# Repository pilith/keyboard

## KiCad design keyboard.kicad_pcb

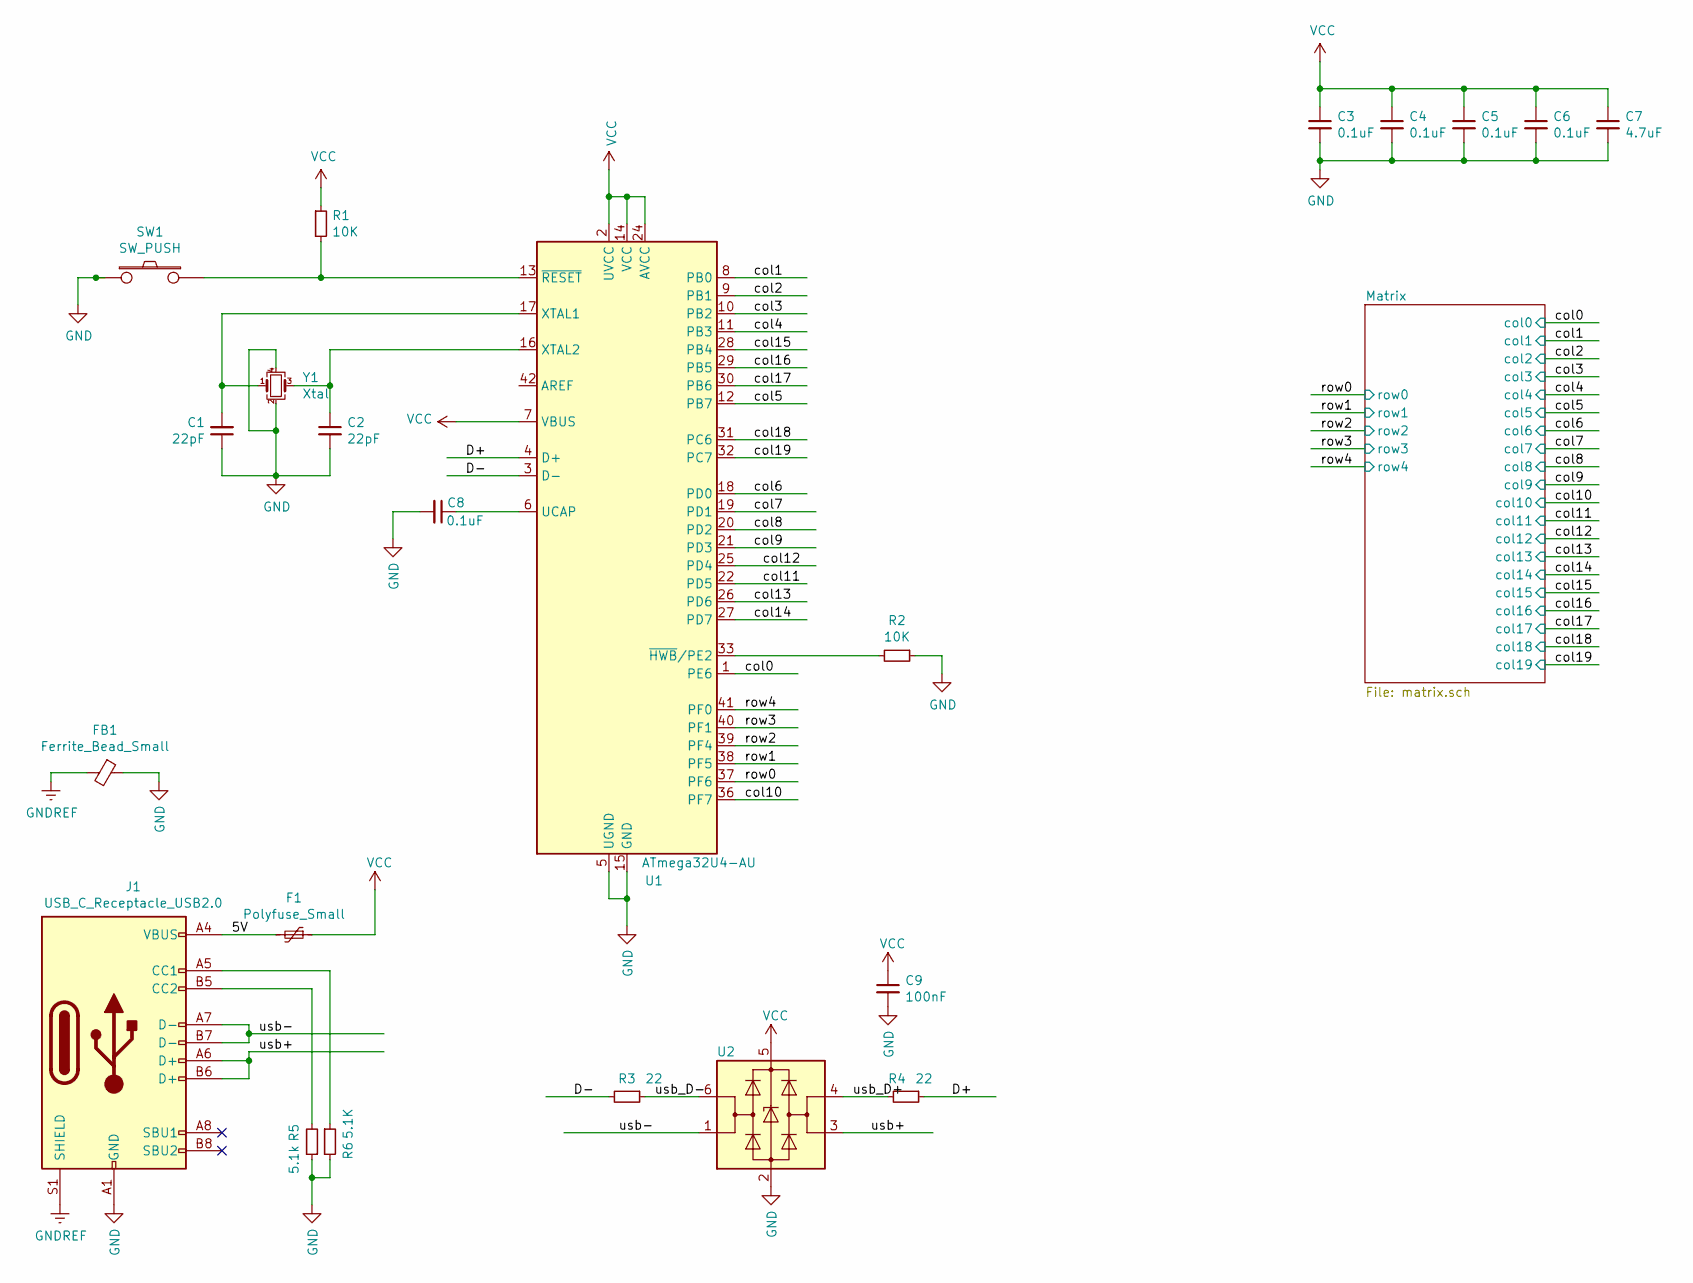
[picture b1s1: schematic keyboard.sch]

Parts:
C1, C2: 22pF; C_0603_1608Metric
C3, C4, C5, C6, C8: 0.1uF; C_0603_1608Metric
C7: 4.7uF; C_0603_1608Metric
C9: 100nF; C_0402_1005Metric
F1: Polyfuse_Small; Fuse_0805_2012Metric
FB1: Ferrite_Bead_Small; L_0805_2012Metric_Pad1.15x1.40mm_HandSolder
J1: USB_C_Receptacle_USB2.0; USB_C_GCT_USB4085
R1, R2: 10K; R_0603_1608Metric
R3, R4: 22; R_0603_1608Metric
R5: 5.1k; R_0603_1608Metric
R6: 5.1K; R_0603_1608Metric
SW1: SW_PUSH; SW_SPST_SKQG_WithStem
U1: ATmega32U4-AU; TQFP-44_10x10mm_P0.8mm
U2: USBLC6-2SC6; SOT-23-6
Y1: Xtal; Crystal_SMD_3225-4Pin_3.2x2.5mm_HandSoldering

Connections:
/5V: F1.2, J1.A4 (VBUS), J1.A9 (VBUS), J1.B4 (VBUS), J1.B9 (VBUS)
/D+: R4.1, U1.4 (D+)
/D-: R3.2, U1.3 (D-)
/col0: U1.1 (PE6); also elsewhere on the board
/col1: U1.8 (PB0); also elsewhere on the board
/col2: U1.9 (PB1); also elsewhere on the board
/col3: U1.10 (PB2); also elsewhere on the board
/col4: U1.11 (PB3); also elsewhere on the board
/col5: U1.12 (PB7); also elsewhere on the board
/col6: U1.18 (PD0); also elsewhere on the board
/col7: U1.19 (PD1); also elsewhere on the board
/col8: U1.20 (PD2); also elsewhere on the board
/col9: U1.21 (PD3); also elsewhere on the board
/col10: U1.36 (PF7); also elsewhere on the board
/col11: U1.22 (PD5); also elsewhere on the board
/col12: U1.25 (PD4); also elsewhere on the board
/col13: U1.26 (PD6); also elsewhere on the board
/col14: U1.27 (PD7); also elsewhere on the board
/col15: U1.28 (PB4); also elsewhere on the board
/col16: U1.29 (PB5); also elsewhere on the board
/col17: U1.30 (PB6); also elsewhere on the board
/col18: U1.31 (PC6); also elsewhere on the board
/col19: U1.32 (PC7); also elsewhere on the board
/row0: U1.37 (PF6); also elsewhere on the board
/row1: U1.38 (PF5); also elsewhere on the board
/row2: U1.39 (PF4); also elsewhere on the board
/row3: U1.40 (PF1); also elsewhere on the board
/row4: U1.41 (PF0); also elsewhere on the board
/usb+: J1.A6 (D+), J1.B6 (D+), U2.3 (I/O2)
/usb-: J1.A7 (D-), J1.B7 (D-), U2.1 (I/O1)
/usb_D+: R4.2, U2.4 (I/O2)
/usb_D-: R3.1, U2.6 (I/O1)
GND: C1.1, C2.2, C3.2, C4.2, C5.2, C6.2, C7.2, C8.2, C9.2, FB1.1, J1.A1 (GND), J1.A12 (GND), J1.B1 (GND), J1.B12 (GND), R2.1, R5.1, R6.2, SW1.1, U1.5 (UGND), U1.15 (GND), U1.23 (GND), U1.35 (GND), U1.43 (GND), U2.2 (GND), Y1.2, Y1.4
GNDREF: FB1.2, J1.S1 (SHIELD)
unnamed: C1.2, U1.17 (XTAL1), Y1.1
unnamed: C2.1, U1.16 (XTAL2), Y1.3
unnamed: C8.1, U1.6 (UCAP)
unnamed: J1.A5 (CC1), R6.1
unnamed: J1.B5 (CC2), R5.2
unnamed: R1.2, SW1.2, U1.13 (~RESET)
unnamed: R2.2, U1.33 (~HWB~/PE2)
VCC: C3.1, C4.1, C5.1, C6.1, C7.1, C9.1, F1.1, R1.1, U1.2 (UVCC), U1.7 (VBUS), U1.14 (VCC), U1.24 (AVCC), U1.34 (VCC), U1.44 (AVCC), U2.5 (VBUS)

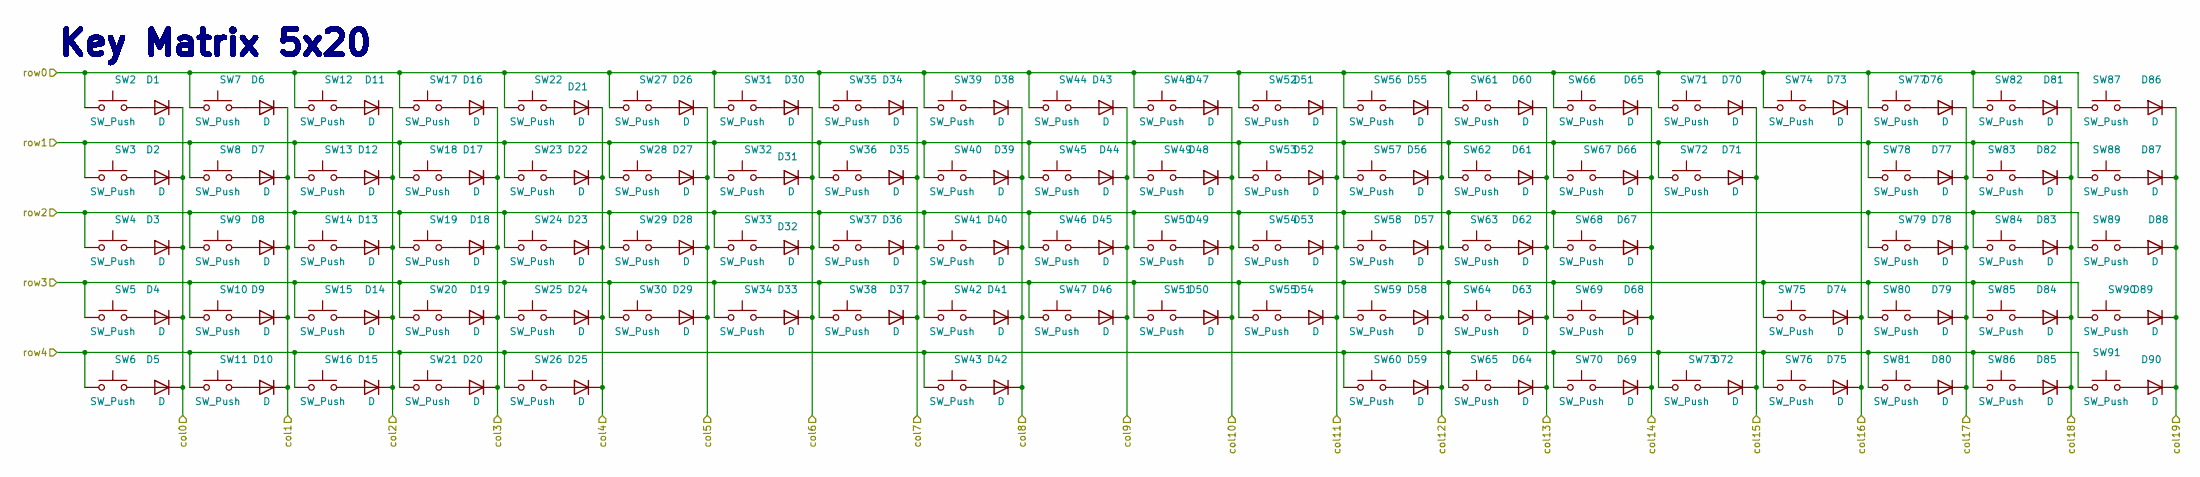
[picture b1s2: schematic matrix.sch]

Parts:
D1, D2, D3, D4, D5, D6, D7, D8, D9, D10, D11, D12, D13, D14, D15, D16, D17, D18, D19, D20, D21, D22, D23, D24, D25, D26, D27, D28, D29, D30, D31, D32, D33, D34, D35, D36, D37, D38, D39, D40, D41, D42, D43, D44, D45, D46, D47, D48, D49, D50, D51, D52, D53, D54, D55, D56, D57, D58, D59, D60, D61, D62, D63, D64, D65, D66, D67, D68, D69, D70, D71, D72, D73, D74, D75, D76, D77, D78, D79, D80, D81, D82, D83, D84, D85, D86, D87, D88, D89, D90: D; D_SOD-123
SW2, SW3, SW4, SW5, SW6, SW7, SW8, SW9, SW10, SW11, SW12, SW17, SW18, SW19, SW20, SW22, SW23, SW24, SW25, SW27, SW28, SW29, SW30, SW31, SW32, SW33, SW34, SW35, SW36, SW37, SW38, SW39, SW40, SW41, SW42, SW44, SW45, SW46, SW47, SW48, SW49, SW50, SW51, SW52, SW53, SW54, SW55, SW56, SW57, SW58, SW59, SW61, SW62, SW63, SW64, SW66, SW67, SW68, SW73, SW74, SW75, SW76, SW77, SW78, SW79, SW80, SW81, SW82, SW83, SW84, SW85, SW86, SW87, SW88, SW89, SW90, SW91: SW_Push; SW_Cherry_MX_1.00u_Plate
SW13: SW_Push; SW_Cherry_MX_1.50u_Plate
SW14: SW_Push; SW_Cherry_MX_1.75u_Plate
SW15, SW16, SW21, SW26, SW60, SW65, SW70: SW_Push; SW_Cherry_MX_1.25u_Plate
SW43: SW_Push; SW_Cherry_MX_6.25u_Plate
SW69: SW_Push; SW_Cherry_MX_2.75u_Plate
SW71: SW_Push; SW_Cherry_MX_2.00u_Plate
SW72: SW_Push; SW_Cherry_MX_ISOEnter_Plate

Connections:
/col0: D1.1 (K), D2.1 (K), D3.1 (K), D4.1 (K), D5.1 (K); also elsewhere on the board
/col1: D6.1 (K), D7.1 (K), D8.1 (K), D9.1 (K), D10.1 (K); also elsewhere on the board
/col2: D11.1 (K), D12.1 (K), D13.1 (K), D14.1 (K), D15.1 (K); also elsewhere on the board
/col3: D16.1 (K), D17.1 (K), D18.1 (K), D19.1 (K), D20.1 (K); also elsewhere on the board
/col4: D21.1 (K), D22.1 (K), D23.1 (K), D24.1 (K), D25.1 (K); also elsewhere on the board
/col5: D26.1 (K), D27.1 (K), D28.1 (K), D29.1 (K); also elsewhere on the board
/col6: D30.1 (K), D31.1 (K), D32.1 (K), D33.1 (K); also elsewhere on the board
/col7: D34.1 (K), D35.1 (K), D36.1 (K), D37.1 (K); also elsewhere on the board
/col8: D38.1 (K), D39.1 (K), D40.1 (K), D41.1 (K), D42.1 (K); also elsewhere on the board
/col9: D43.1 (K), D44.1 (K), D45.1 (K), D46.1 (K); also elsewhere on the board
/col10: D47.1 (K), D48.1 (K), D49.1 (K), D50.1 (K); also elsewhere on the board
/col11: D51.1 (K), D52.1 (K), D53.1 (K), D54.1 (K); also elsewhere on the board
/col12: D55.1 (K), D56.1 (K), D57.1 (K), D58.1 (K), D59.1 (K); also elsewhere on the board
/col13: D60.1 (K), D61.1 (K), D62.1 (K), D63.1 (K), D64.1 (K); also elsewhere on the board
/col14: D65.1 (K), D66.1 (K), D67.1 (K), D68.1 (K), D69.1 (K); also elsewhere on the board
/col15: D70.1 (K), D71.1 (K), D72.1 (K); also elsewhere on the board
/col16: D73.1 (K), D74.1 (K), D75.1 (K); also elsewhere on the board
/col17: D76.1 (K), D77.1 (K), D78.1 (K), D79.1 (K), D80.1 (K); also elsewhere on the board
/col18: D81.1 (K), D82.1 (K), D83.1 (K), D84.1 (K), D85.1 (K); also elsewhere on the board
/col19: D86.1 (K), D87.1 (K), D88.1 (K), D89.1 (K), D90.1 (K); also elsewhere on the board
/row0: SW2.1, SW7.1, SW12.1, SW17.1, SW22.1, SW27.1, SW31.1, SW35.1, SW39.1, SW44.1, SW48.1, SW52.1, SW56.1, SW61.1, SW66.1, SW71.1, SW74.1, SW77.1, SW82.1, SW87.1; also elsewhere on the board
/row1: SW3.1, SW8.1, SW13.1, SW18.1, SW23.1, SW28.1, SW32.1, SW36.1, SW40.1, SW45.1, SW49.1, SW53.1, SW57.1, SW62.1, SW67.1, SW72.1, SW78.1, SW83.1, SW88.1; also elsewhere on the board
/row2: SW4.1, SW9.1, SW14.1, SW19.1, SW24.1, SW29.1, SW33.1, SW37.1, SW41.1, SW46.1, SW50.1, SW54.1, SW58.1, SW63.1, SW68.1, SW79.1, SW84.1, SW89.1; also elsewhere on the board
/row3: SW5.1, SW10.1, SW15.1, SW20.1, SW25.1, SW30.1, SW34.1, SW38.1, SW42.1, SW47.1, SW51.1, SW55.1, SW59.1, SW64.1, SW69.1, SW75.1, SW80.1, SW85.1, SW90.1; also elsewhere on the board
/row4: SW6.1, SW11.1, SW16.1, SW21.1, SW26.1, SW43.1, SW60.1, SW65.1, SW70.1, SW73.1, SW76.1, SW81.1, SW86.1, SW91.1; also elsewhere on the board
unnamed: D1.2 (A), SW2.2
unnamed: D2.2 (A), SW3.2
unnamed: D3.2 (A), SW4.2
unnamed: D4.2 (A), SW5.2
unnamed: D5.2 (A), SW6.2
unnamed: D6.2 (A), SW7.2
unnamed: D7.2 (A), SW8.2
unnamed: D8.2 (A), SW9.2
unnamed: D9.2 (A), SW10.2
unnamed: D10.2 (A), SW11.2
unnamed: D11.2 (A), SW12.2
unnamed: D12.2 (A), SW13.2
unnamed: D13.2 (A), SW14.2
unnamed: D14.2 (A), SW15.2
unnamed: D15.2 (A), SW16.2
unnamed: D16.2 (A), SW17.2
unnamed: D17.2 (A), SW18.2
unnamed: D18.2 (A), SW19.2
unnamed: D19.2 (A), SW20.2
unnamed: D20.2 (A), SW21.2
unnamed: D21.2 (A), SW22.2
unnamed: D22.2 (A), SW23.2
unnamed: D23.2 (A), SW24.2
unnamed: D24.2 (A), SW25.2
unnamed: D25.2 (A), SW26.2
unnamed: D26.2 (A), SW27.2
unnamed: D27.2 (A), SW28.2
unnamed: D28.2 (A), SW29.2
unnamed: D29.2 (A), SW30.2
unnamed: D30.2 (A), SW31.2
unnamed: D31.2 (A), SW32.2
unnamed: D32.2 (A), SW33.2
unnamed: D33.2 (A), SW34.2
unnamed: D34.2 (A), SW35.2
unnamed: D35.2 (A), SW36.2
unnamed: D36.2 (A), SW37.2
unnamed: D37.2 (A), SW38.2
unnamed: D38.2 (A), SW39.2
unnamed: D39.2 (A), SW40.2
unnamed: D40.2 (A), SW41.2
unnamed: D41.2 (A), SW42.2
unnamed: D42.2 (A), SW43.2
unnamed: D43.2 (A), SW44.2
unnamed: D44.2 (A), SW45.2
unnamed: D45.2 (A), SW46.2
unnamed: D46.2 (A), SW47.2
unnamed: D47.2 (A), SW48.2
unnamed: D48.2 (A), SW49.2
unnamed: D49.2 (A), SW50.2
unnamed: D50.2 (A), SW51.2
unnamed: D51.2 (A), SW52.2
unnamed: D52.2 (A), SW53.2
unnamed: D53.2 (A), SW54.2
unnamed: D54.2 (A), SW55.2
unnamed: D55.2 (A), SW56.2
unnamed: D56.2 (A), SW57.2
unnamed: D57.2 (A), SW58.2
unnamed: D58.2 (A), SW59.2
unnamed: D59.2 (A), SW60.2
unnamed: D60.2 (A), SW61.2
unnamed: D61.2 (A), SW62.2
unnamed: D62.2 (A), SW63.2
unnamed: D63.2 (A), SW64.2
unnamed: D64.2 (A), SW65.2
unnamed: D65.2 (A), SW66.2
unnamed: D66.2 (A), SW67.2
unnamed: D67.2 (A), SW68.2
unnamed: D68.2 (A), SW69.2
unnamed: D69.2 (A), SW70.2
unnamed: D70.2 (A), SW71.2
unnamed: D71.2 (A), SW72.2
unnamed: D72.2 (A), SW73.2
unnamed: D73.2 (A), SW74.2
unnamed: D74.2 (A), SW75.2
unnamed: D75.2 (A), SW76.2
unnamed: D76.2 (A), SW77.2
unnamed: D77.2 (A), SW78.2
unnamed: D78.2 (A), SW79.2
unnamed: D79.2 (A), SW80.2
unnamed: D80.2 (A), SW81.2
unnamed: D81.2 (A), SW82.2
unnamed: D82.2 (A), SW83.2
unnamed: D83.2 (A), SW84.2
unnamed: D84.2 (A), SW85.2
unnamed: D85.2 (A), SW86.2
unnamed: D86.2 (A), SW87.2
unnamed: D87.2 (A), SW88.2
unnamed: D88.2 (A), SW89.2
unnamed: D89.2 (A), SW90.2
unnamed: D90.2 (A), SW91.2

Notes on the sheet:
Key Matrix 5x20

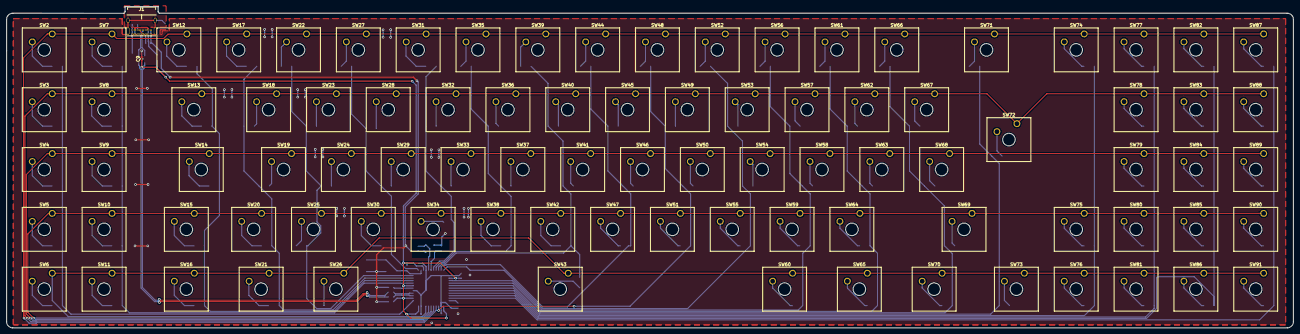
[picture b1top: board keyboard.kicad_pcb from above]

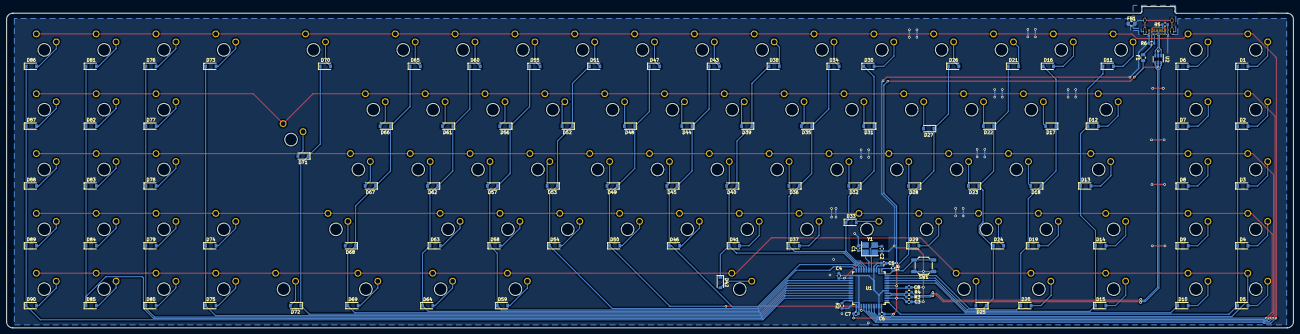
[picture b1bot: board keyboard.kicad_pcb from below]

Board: 2 copper layers, 409.8 x 102.3 mm, 202 parts (110 on the bottom side), 132 nets.

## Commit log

2021-06-01 added bom html file
2021-06-09 added QMK files and compiled hex
